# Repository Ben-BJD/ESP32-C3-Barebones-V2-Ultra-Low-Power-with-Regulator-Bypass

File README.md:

# ESP32-C3 Bare Bones (V2): Ultra-Low Power with Regulator Bypass - KiCAD Source Files

Fig 1 - Assembled Board
---

Fig 2 - 3D view of Board
---

## Overview

This repository contains the KiCAD source files for the **ESP32-C3 Bare Bones Mini (V2)**, a compact, versatile, and ultra-low-power development board.

This project is a significant evolution of the [original "Bare Bones" design](https://github.com/Ben-BJD/esp32-c3-bare-bones), engineered for maximum power efficiency and flexibility. It features a unique dual-mode power system, a 4-layer PCB for improved RF performance, and a compact form factor with castellated edges, making it ideal for both battery-powered IoT prototypes and integration into larger projects.

The design prioritizes hand-assembly by using 0805 and larger SMD components where possible.

## Key Features

*   **Dual Power Modes:** A slide switch selects between a regulated input (REG on the board) for standard LiPo batteries/USB power or a direct-to-MCU bypass for ultra-low-power LiFePO4 operation (DIR on the board).
*   **Ultra-Low Deep Sleep:** Designed to achieve ~5µA deep sleep current in Direct Mode by bypassing the voltage regulator entirely.
*   **Compact & Integratable:** A minimal footprint with castellated holes on the edges allows the board to be soldered directly as a module onto a parent PCB (or solder header pins).
*   **ESP32-C3 Antenna Support:** The layout accommodates both the standard ESP32-C3-MINI-1 with a PCB antenna (overhanging the board) and the ESP32-C3-MINI-1U variant with a U.FL connector for an external antenna.
*   **Onboard Connectors:** Includes a JST-PH connector for batteries and a dedicated 4-pin header for easy programming.
*   **Improved RF Performance:** A 4-layer PCB with dedicated ground and power planes helps reduce noise and improve radio signal integrity.
*   **Hand-Solder Friendly:** Uses larger 0805 components for capacitors and resistors, making it easier to assemble by hand.

## Power System Explained

The board's most unique feature is its slide-switch-controlled dual power system.

### 1. Regulated Mode (for LiPo / 5V USB) [REG]
In this mode, power from the JST connector is routed through the onboard **RT9080 Low-Dropout (LDO) regulator**. This allows you to safely power the board with a standard 3.7V (4.2V max) LiPo battery or a 5V USB power source. This mode is ideal for development or applications where the LDO's quiescent current (typically a few microamps) is acceptable.

### 2. Direct Mode (for LiFePO4 - Ultra-Low Power) [DIR]
This mode **bypasses the LDO regulator entirely**, connecting the battery's positive terminal directly to the ESP32-C3's 3.3V rail. This eliminates the regulator's quiescent current, allowing the board to achieve its lowest possible deep sleep power consumption (~5µA). This mode is specifically designed for 3.2V (nominal) LiFePO4 batteries.

> #### ⚠️ **CRITICAL SAFETY WARNING** ⚠️
> In **Direct Mode**, there is **NO** onboard over-voltage protection. The input voltage must **NEVER exceed 3.6V**, as this will permanently damage the ESP32-C3 chip.
>
> *   Standard LiPo/Li-ion batteries (4.2V max) **CANNOT** be used in this mode.
> *   You **MUST** use a 3.2V LiFePO4 battery. Ideally charged with an external Battery Management System (BMS) that has a high-voltage cutoff at or below 3.6V. You can always test the batteries voltage first. If over 3.6V wait for it to discharge or apply small load with an LED for a few minutes.
> *   If you are unsure, always use Regulated Mode or measure the battery voltage before connecting it in Direct Mode.

## Programming

The board does not have a USB-to-UART converter to save power. You must program it using an external 3.3V FTDI programmer connected to the 4-pin `PROG` header.

Connect your FTDI programmer as follows:
*   GND -> GND
*   VCC -> 3V3 (or 5V if using Regulated Mode)
*   TX -> RX
*   RX -> TX

To enter bootloader mode, hold down the `BOOT` button, press and release the `RESET` button, and then release the `BOOT` button.

---

## Resources

*   **ESP32-C3-MINI-1 MCU Datasheet:** [PDF Link](https://www.espressif.com/sites/default/files/documentation/esp32-c3-mini-1_datasheet_en.pdf)
*   **ESP32-C3 Hardware Design Guidelines:** [Documentation Link](https://www.espressif.com/sites/default/files/documentation/esp32-c3_hardware_design_guidelines_en.pdf)

## Schematic

[PDF Version](esp32-c3-bare-bones-mini-schematic.pdf)

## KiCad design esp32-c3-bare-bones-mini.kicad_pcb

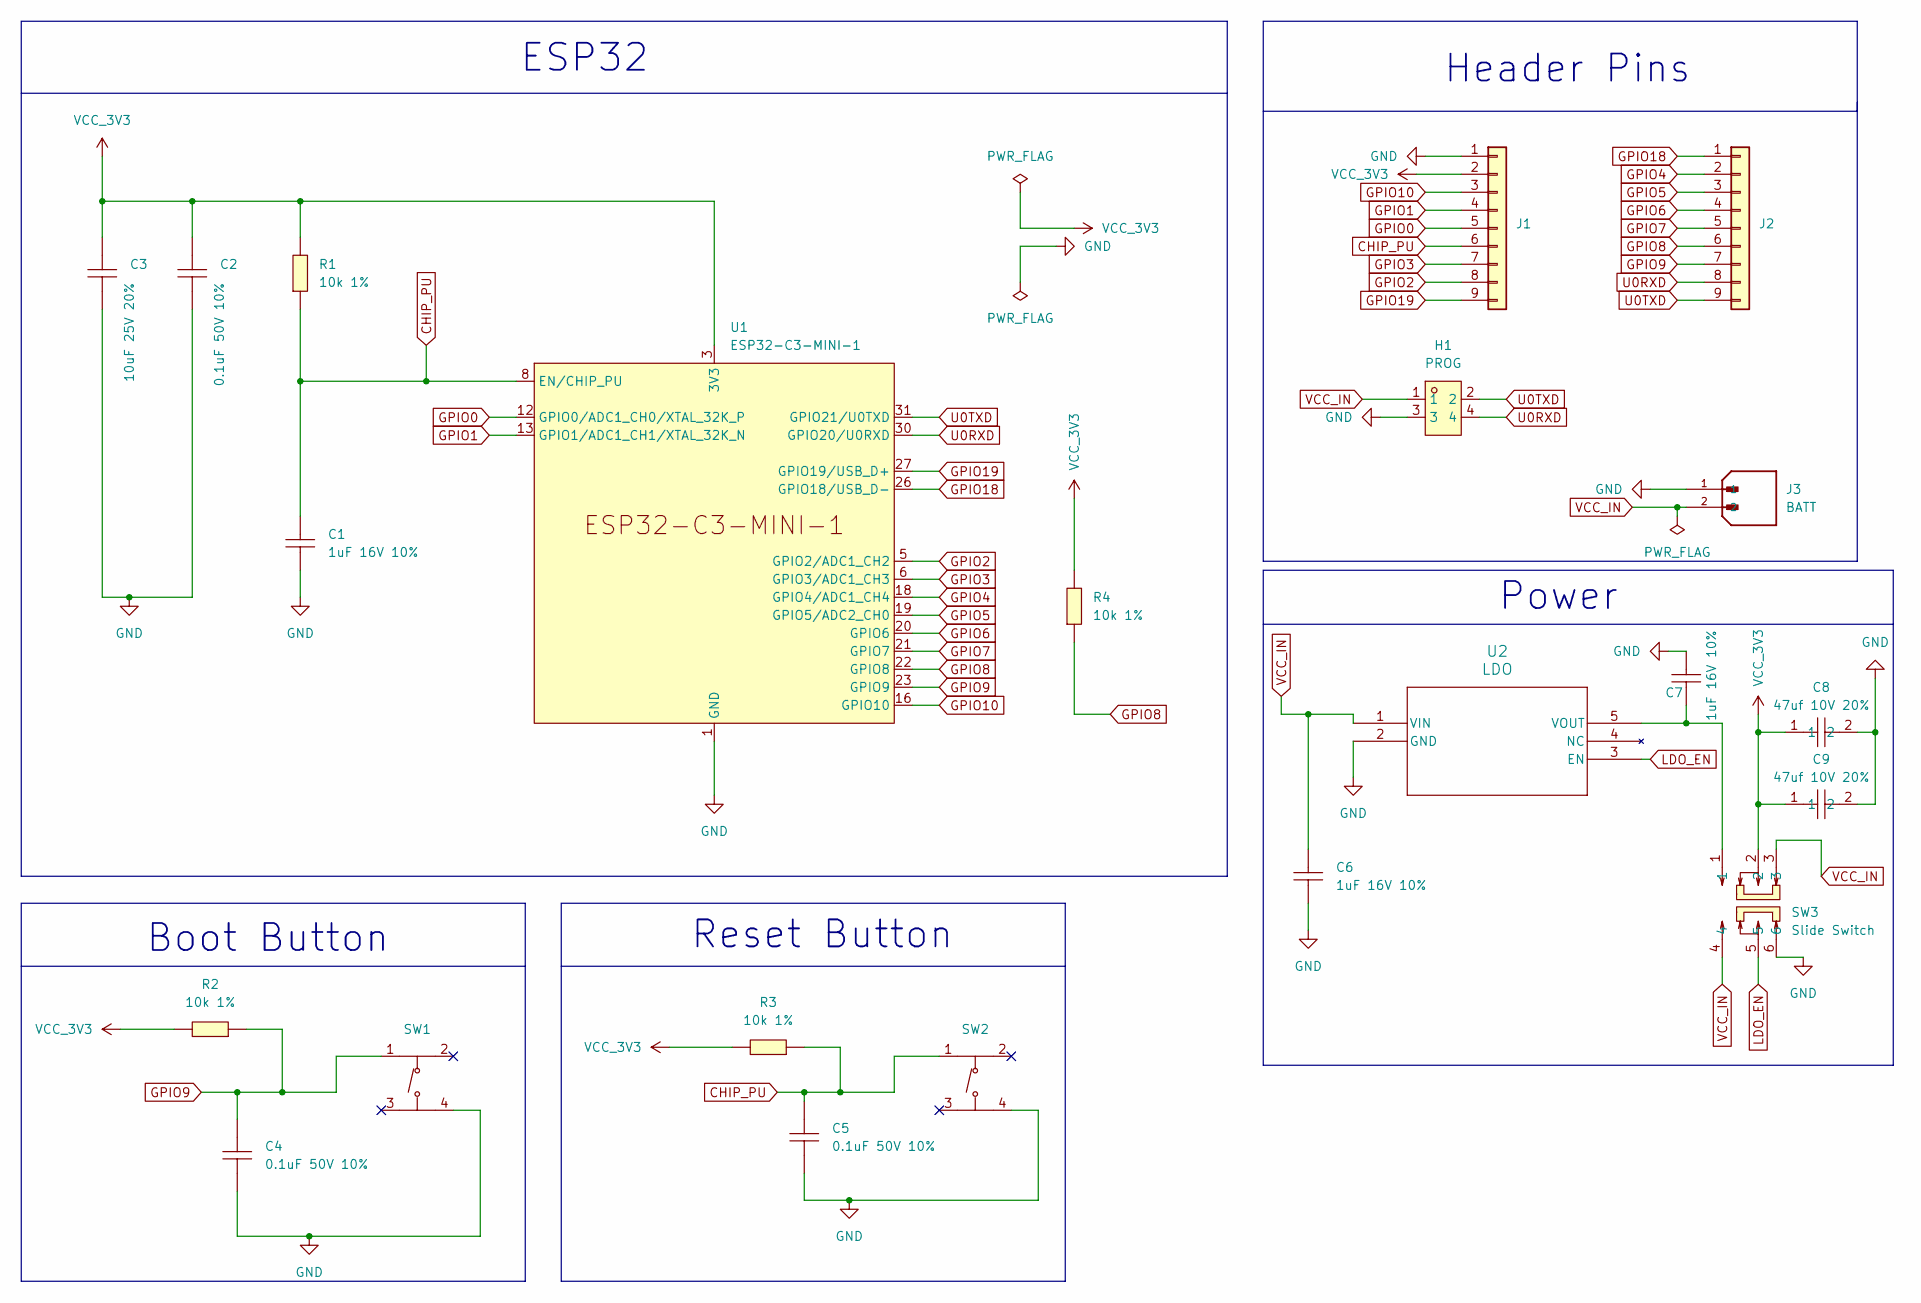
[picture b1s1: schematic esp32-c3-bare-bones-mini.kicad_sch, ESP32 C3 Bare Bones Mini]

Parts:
C1, C6, C7: 1uF 16V 10%; C0805; LCSC Part C24123
C2, C4, C5: 0.1uF 50V 10%; C0805; LCSC Part C476766
C3: 10uF 25V 20%; C0805; LCSC Part C669099
C8, C9: 47uf 10V 20%; C1206; LCSC Part C96123
H1: PROG; HDR-SMD_4P-P2.54-V-M-R2-C2-LS7.5; LCSC Part C919361
J1, J2: Castellated_9Pin_Row
J3: BATT; JST_B2B-PH-SM4-TB; PARTREV N/A; DigiKey_Part_Number 455-B2B-PH-SM4-TBCT-ND
R1, R2, R3, R4: 10k 1%; R0805; LCSC Part C17414
SW1, SW2: SW-SMD_4P-L5.1-W5.1-P3.70-LS6.5-TL_H1.5; LCSC Part C318884
SW3: Slide Switch; SW-SMD_MS-22D28-G020; LCSC Part C963205
U1: ESP32-C3-MINI-1; Part ESP32-C3-MINI-1-H4X(ANT) | ESP32-C3-MIN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
U2: LDO; TSOT-23-5_RIT-M

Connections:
CHIP_PU: C1.2, C5.2, J1.6, R1.1, R3.1, SW2.1 (A), U1.8 (EN/CHIP_PU); also elsewhere on the board
GND: C1.1, C2.1, C3.1, C4.1, C5.1, C6.1, C7.2, C8.2, C9.2, H1.3, J1.1, J3.1, SW1.4 (D), SW2.4 (D), SW3.6, U1.1 (GND), U1.2 (GND), U1.11 (GND), U1.14 (GND), U1.36 (GND), U1.37 (GND), U1.38 (GND), U1.39 (GND), U1.40 (GND), U1.41 (GND), U1.42 (GND), U1.43 (GND), U1.44 (GND), U1.45 (GND), U1.46 (GND), U1.47 (GND), U1.48 (GND), U1.49 (GND), U1.50 (GND), U1.51 (GND), U1.52 (GND), U1.53 (GND), U2.2 (GND); also elsewhere on the board
GPIO0: J1.5, U1.12 (GPIO0/ADC1_CH0/XTAL_32K_P)
GPIO1: J1.4, U1.13 (GPIO1/ADC1_CH1/XTAL_32K_N)
GPIO2: J1.8, U1.5 (GPIO2/ADC1_CH2)
GPIO3: J1.7, U1.6 (GPIO3/ADC1_CH3)
GPIO4: J2.2, U1.18 (GPIO4/ADC1_CH4)
GPIO5: J2.3, U1.19 (GPIO5/ADC2_CH0)
GPIO6: J2.4, U1.20 (GPIO6)
GPIO7: J2.5, U1.21 (GPIO7)
GPIO8: J2.6, R4.1, U1.22 (GPIO8)
GPIO9: C4.2, J2.7, R2.1, SW1.1 (A), U1.23 (GPIO9); also elsewhere on the board
GPIO10: J1.3, U1.16 (GPIO10)
GPIO18: J2.1, U1.26 (GPIO18/USB_D-)
GPIO19: J1.9, U1.27 (GPIO19/USB_D+)
LDO_EN: SW3.5, U2.3 (EN)
unnamed: C7.1, SW3.1, U2.5 (VOUT)
U0RXD: H1.4, J2.8, U1.30 (GPIO20/U0RXD)
U0TXD: H1.2, J2.9, U1.31 (GPIO21/U0TXD)
VCC_3V3: C2.2, C3.2, C8.1, C9.1, J1.2, R1.2, R2.2, R3.2, R4.2, SW3.2, U1.3 (3V3)
VCC_IN: C6.2, H1.1, J3.2, SW3.3, SW3.4, U2.1 (VIN)

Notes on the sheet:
Reset Button
Header Pins
ESP32
Boot Button
Power

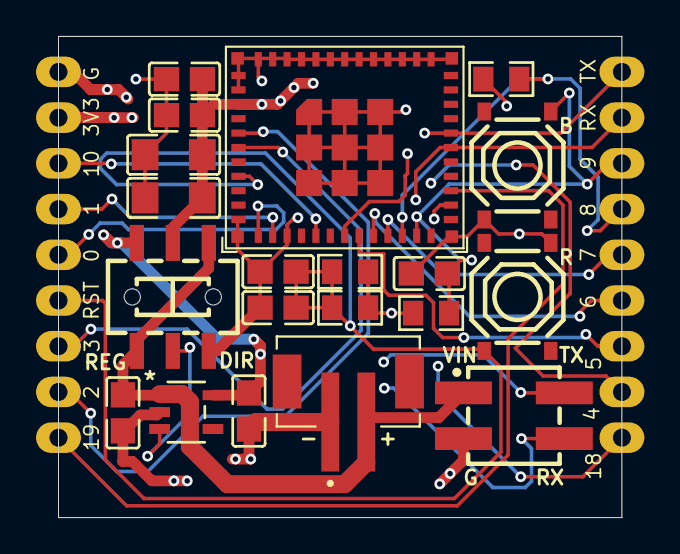
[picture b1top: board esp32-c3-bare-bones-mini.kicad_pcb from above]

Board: 4 copper layers, 31.3 x 26.7 mm, 22 parts (0 on the bottom side), 21 nets.

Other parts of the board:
B: SW-SMD_4P-L5.1-W5.1-P3.70-LS6.5-TL_H1.5
R: SW-SMD_4P-L5.1-W5.1-P3.70-LS6.5-TL_H1.5

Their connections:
CHIP_PU: R.1 (A); also elsewhere on the board
GND: B.4 (D), R.4 (D); also elsewhere on the board
GPIO9: B.1 (A); also elsewhere on the board

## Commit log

2025-12-25 Dual-Mode Power
2026-01-26 Add photo of assembled board
2026-01-31 Add PCBWay project
2026-02-09 Add tutorial
